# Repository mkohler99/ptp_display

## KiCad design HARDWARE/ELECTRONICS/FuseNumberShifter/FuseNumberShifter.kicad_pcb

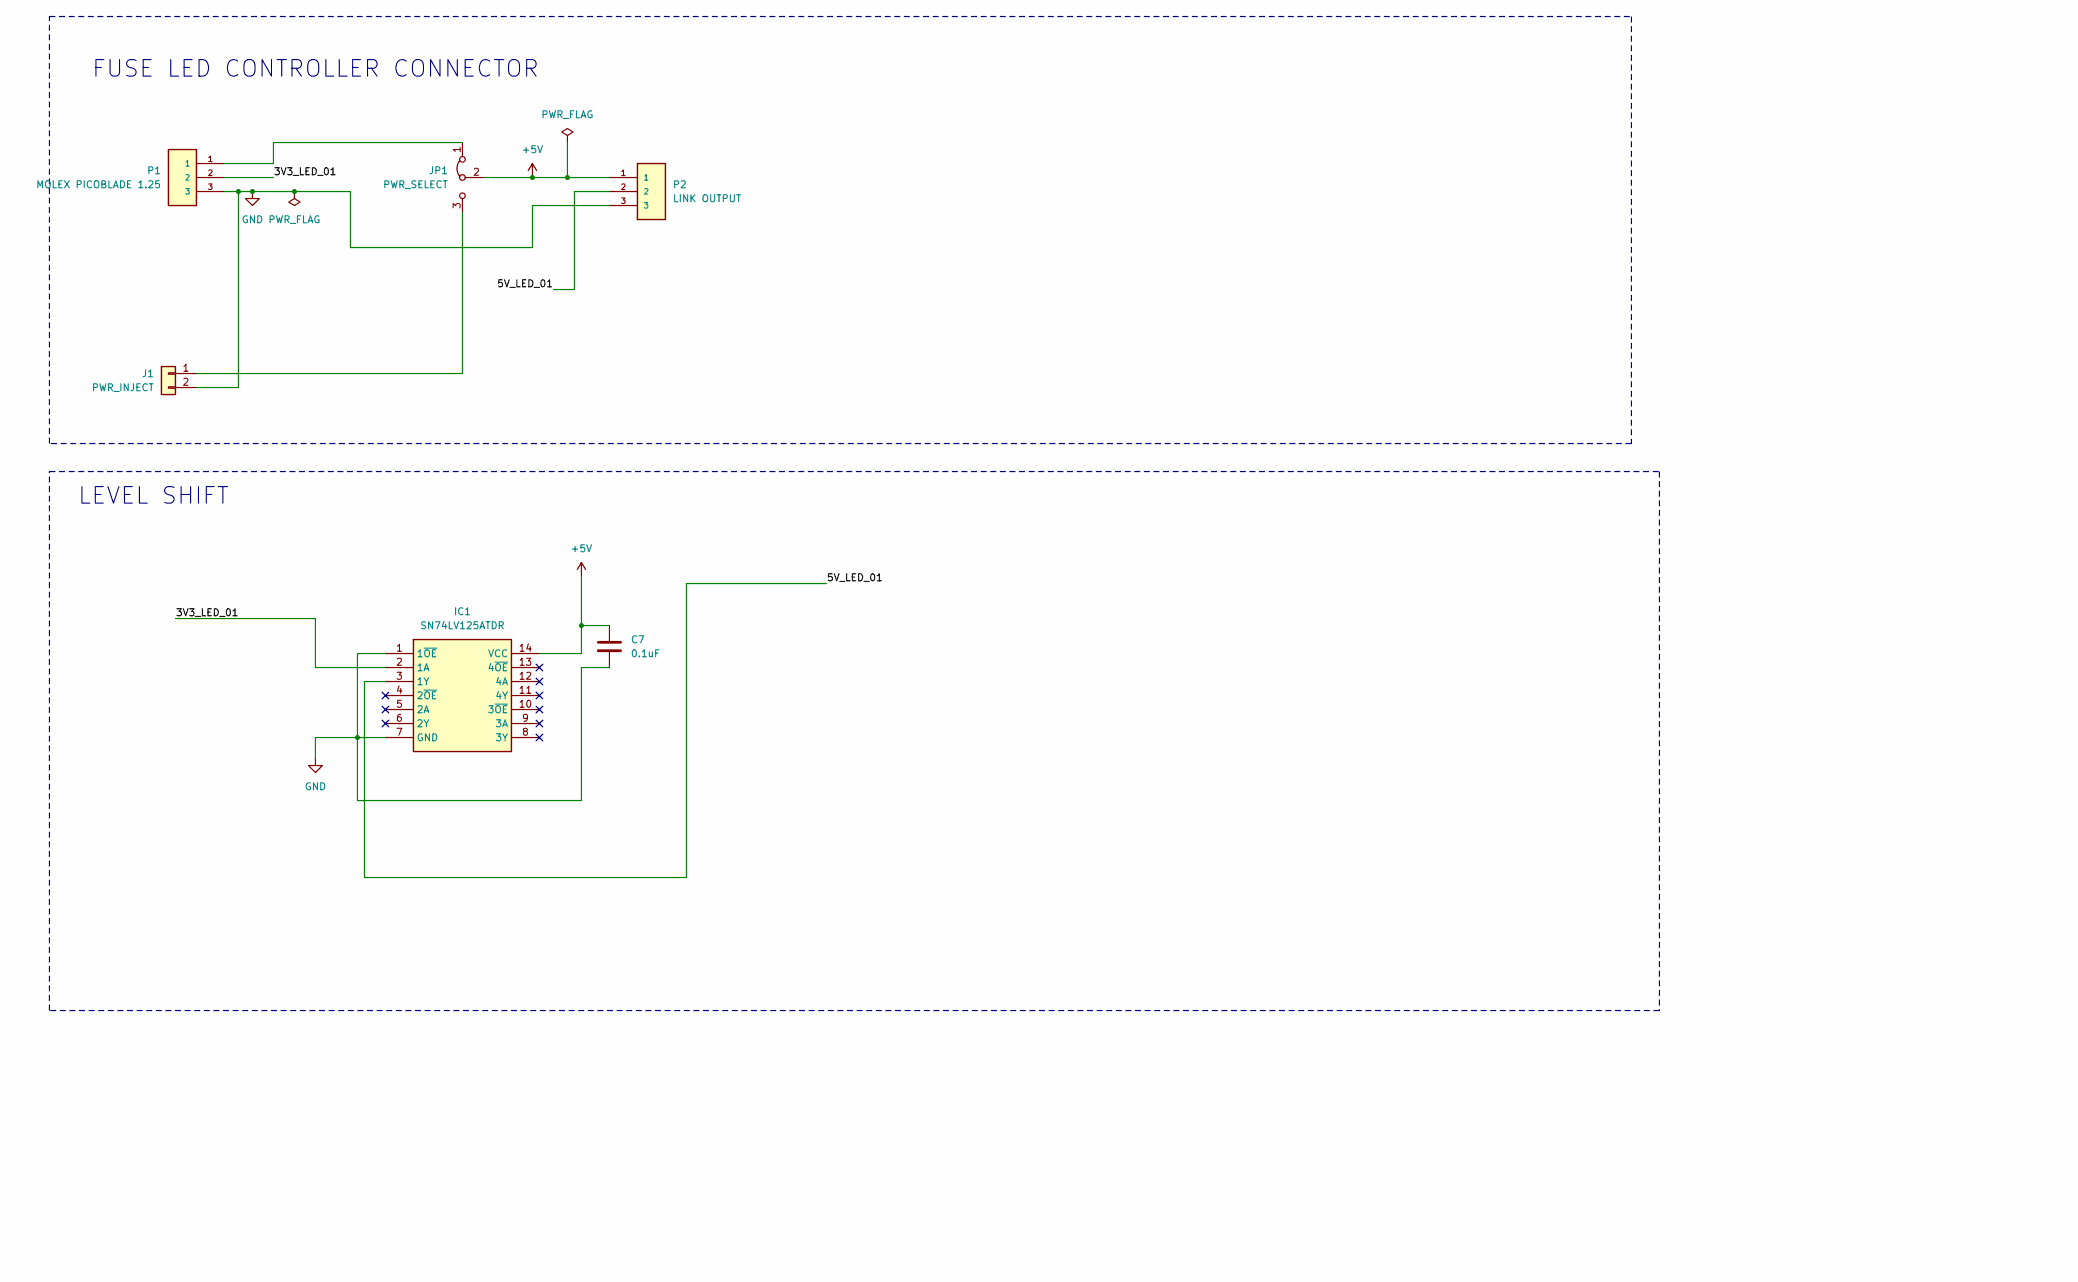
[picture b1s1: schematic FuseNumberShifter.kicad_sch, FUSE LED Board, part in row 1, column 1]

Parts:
C7: 0.1uF; C_0805_2012Metric_Pad1.18x1.45mm_HandSolder
H1, H2, H3, H4: MountingHole; MountingHole_3.2mm_M3
IC1: SN74LV125ATDR; SOIC127P600X175-14N; Mouser Part Number 595-SN74LV125ATDR
J1: PWR_INJECT; PinHeader_1x02_P2.54mm_Horizontal
JP1: PWR_SELECT; SolderJumper-3_P2.0mm_Open_TrianglePad1.0x1.5mm_NumberLabels
P1: MOLEX PICOBLADE 1.25; Molex_PicoBlade_53261-0371_1x03-1MP_P1.25mm_Horizontal
P2: LINK OUTPUT; PinSocket_1x03_P2.54mm_Horizontal

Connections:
+5V: C7.1, IC1.14 (VCC), JP1.2 (C), P2.1
/3V3_LED_01: IC1.2 (1A), P1.2
/5V_LED_01: IC1.3 (1Y), P2.2
GND: C7.2, IC1.1 (1~OE), IC1.7 (GND), J1.2, P1.3, P2.3
unnamed: J1.1, JP1.3 (B)
unnamed: JP1.1 (A), P1.1

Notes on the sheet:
FUSE LED CONTROLLER CONNECTOR
LEVEL SHIFT

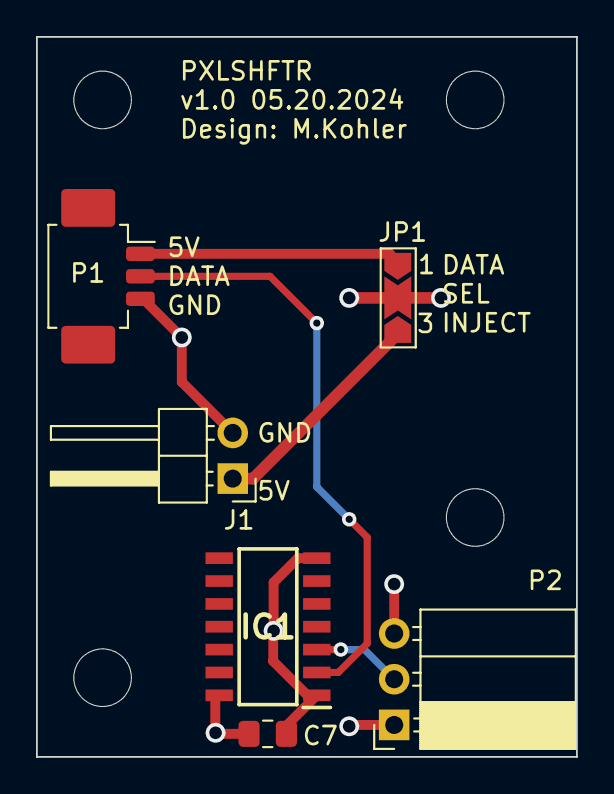
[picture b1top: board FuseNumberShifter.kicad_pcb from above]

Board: 4 copper layers, 30.0 x 40.0 mm, 10 parts (0 on the bottom side), 6 nets.

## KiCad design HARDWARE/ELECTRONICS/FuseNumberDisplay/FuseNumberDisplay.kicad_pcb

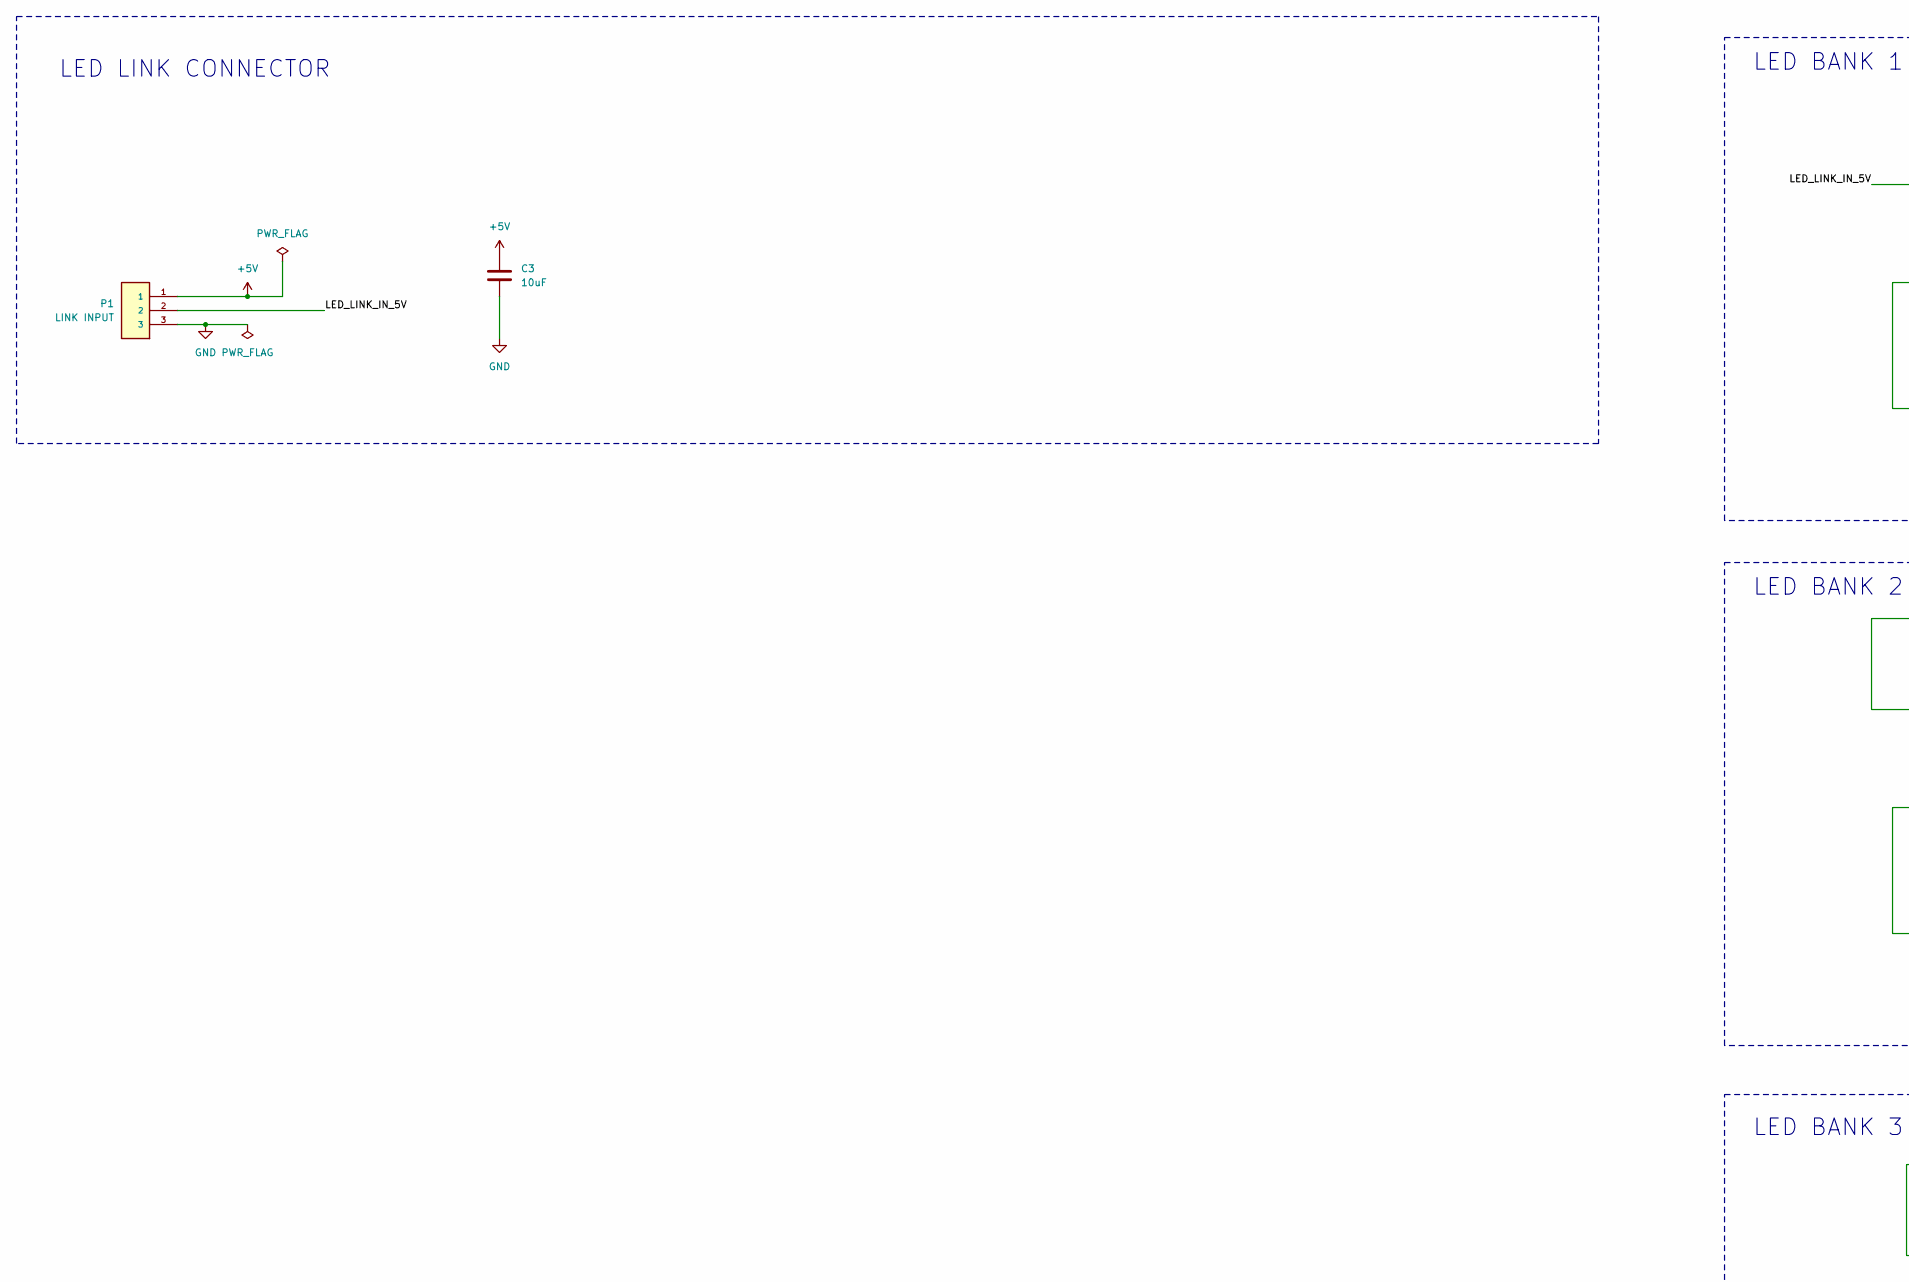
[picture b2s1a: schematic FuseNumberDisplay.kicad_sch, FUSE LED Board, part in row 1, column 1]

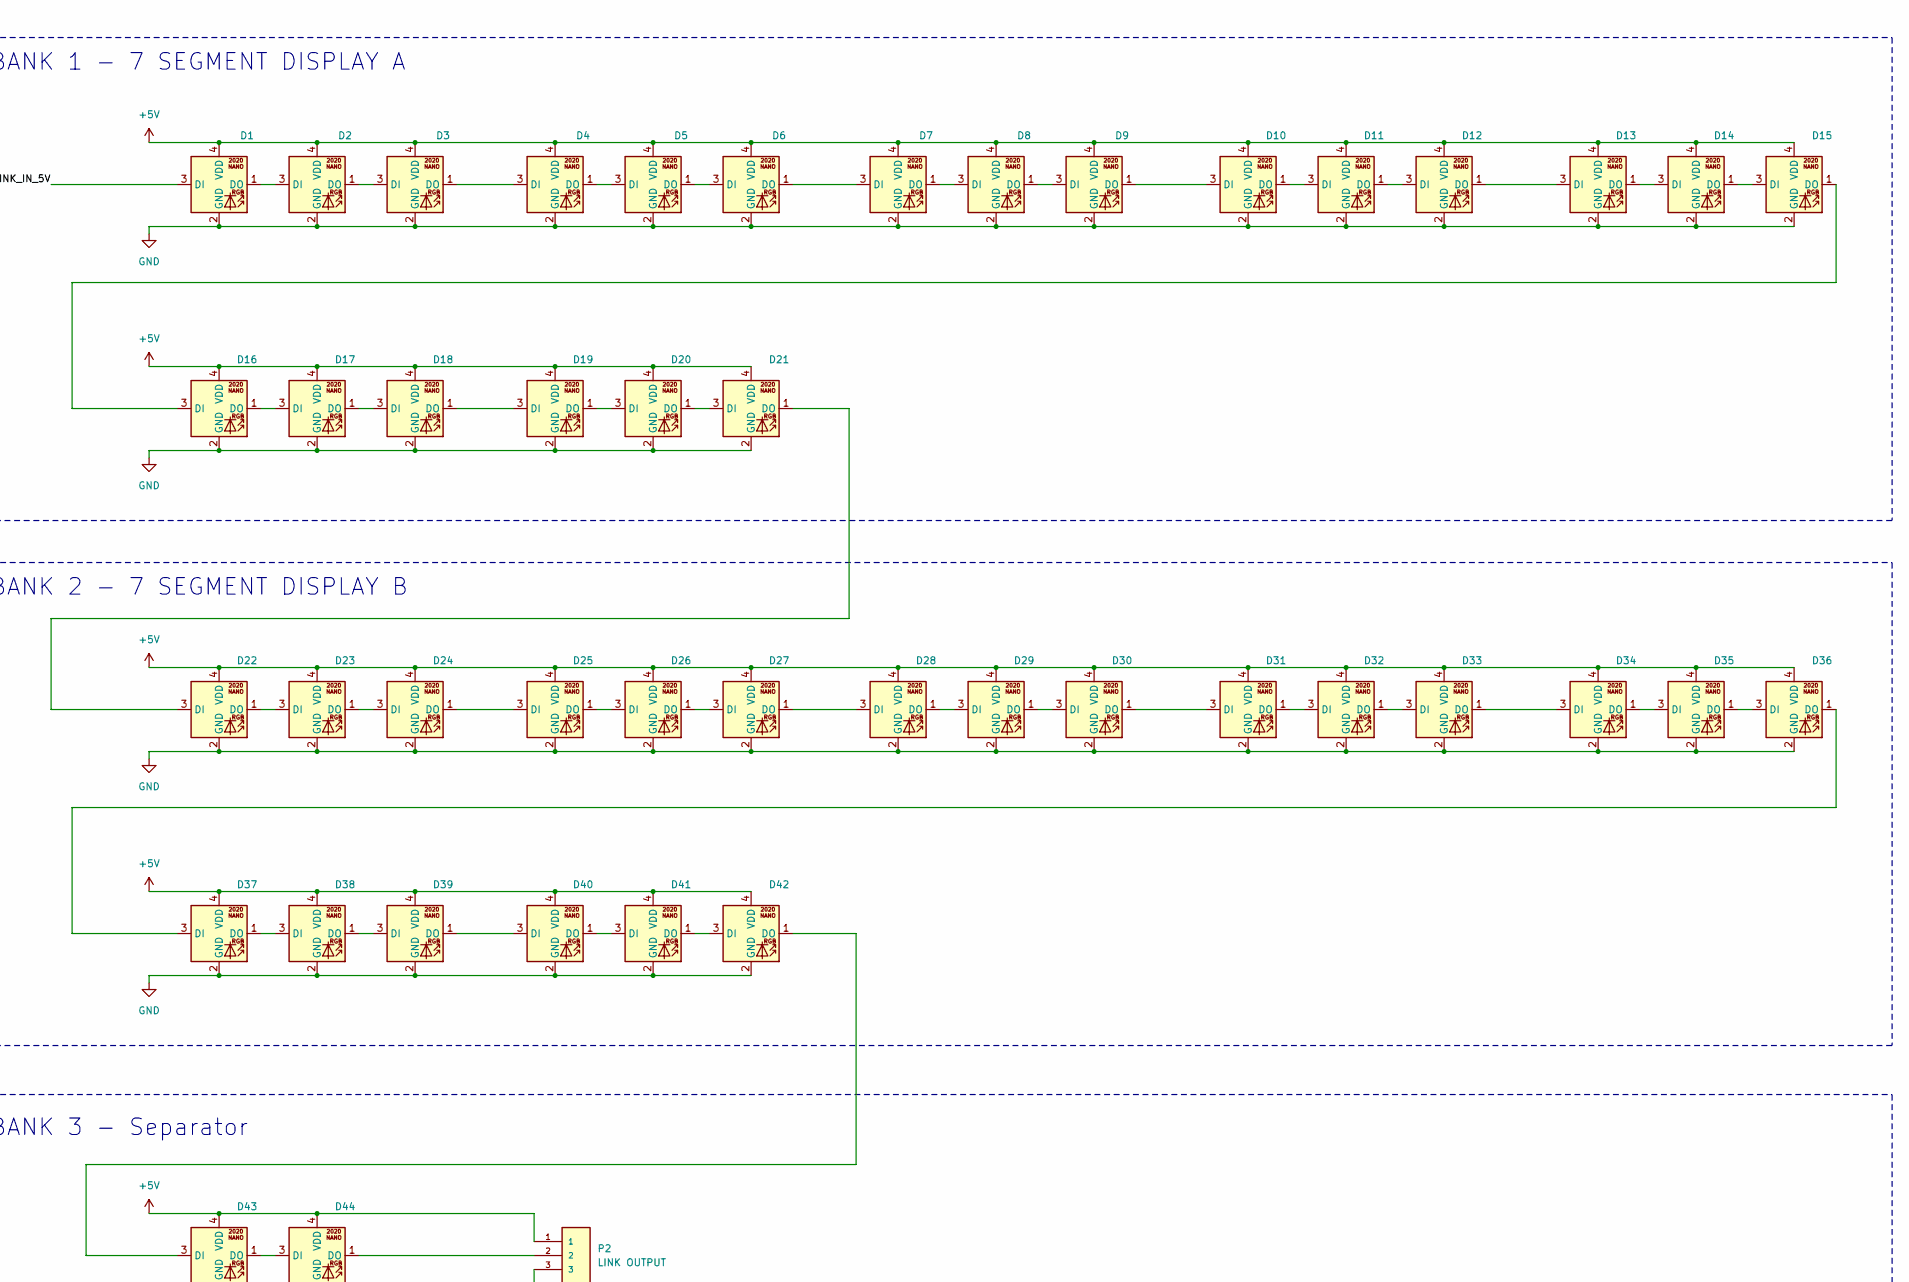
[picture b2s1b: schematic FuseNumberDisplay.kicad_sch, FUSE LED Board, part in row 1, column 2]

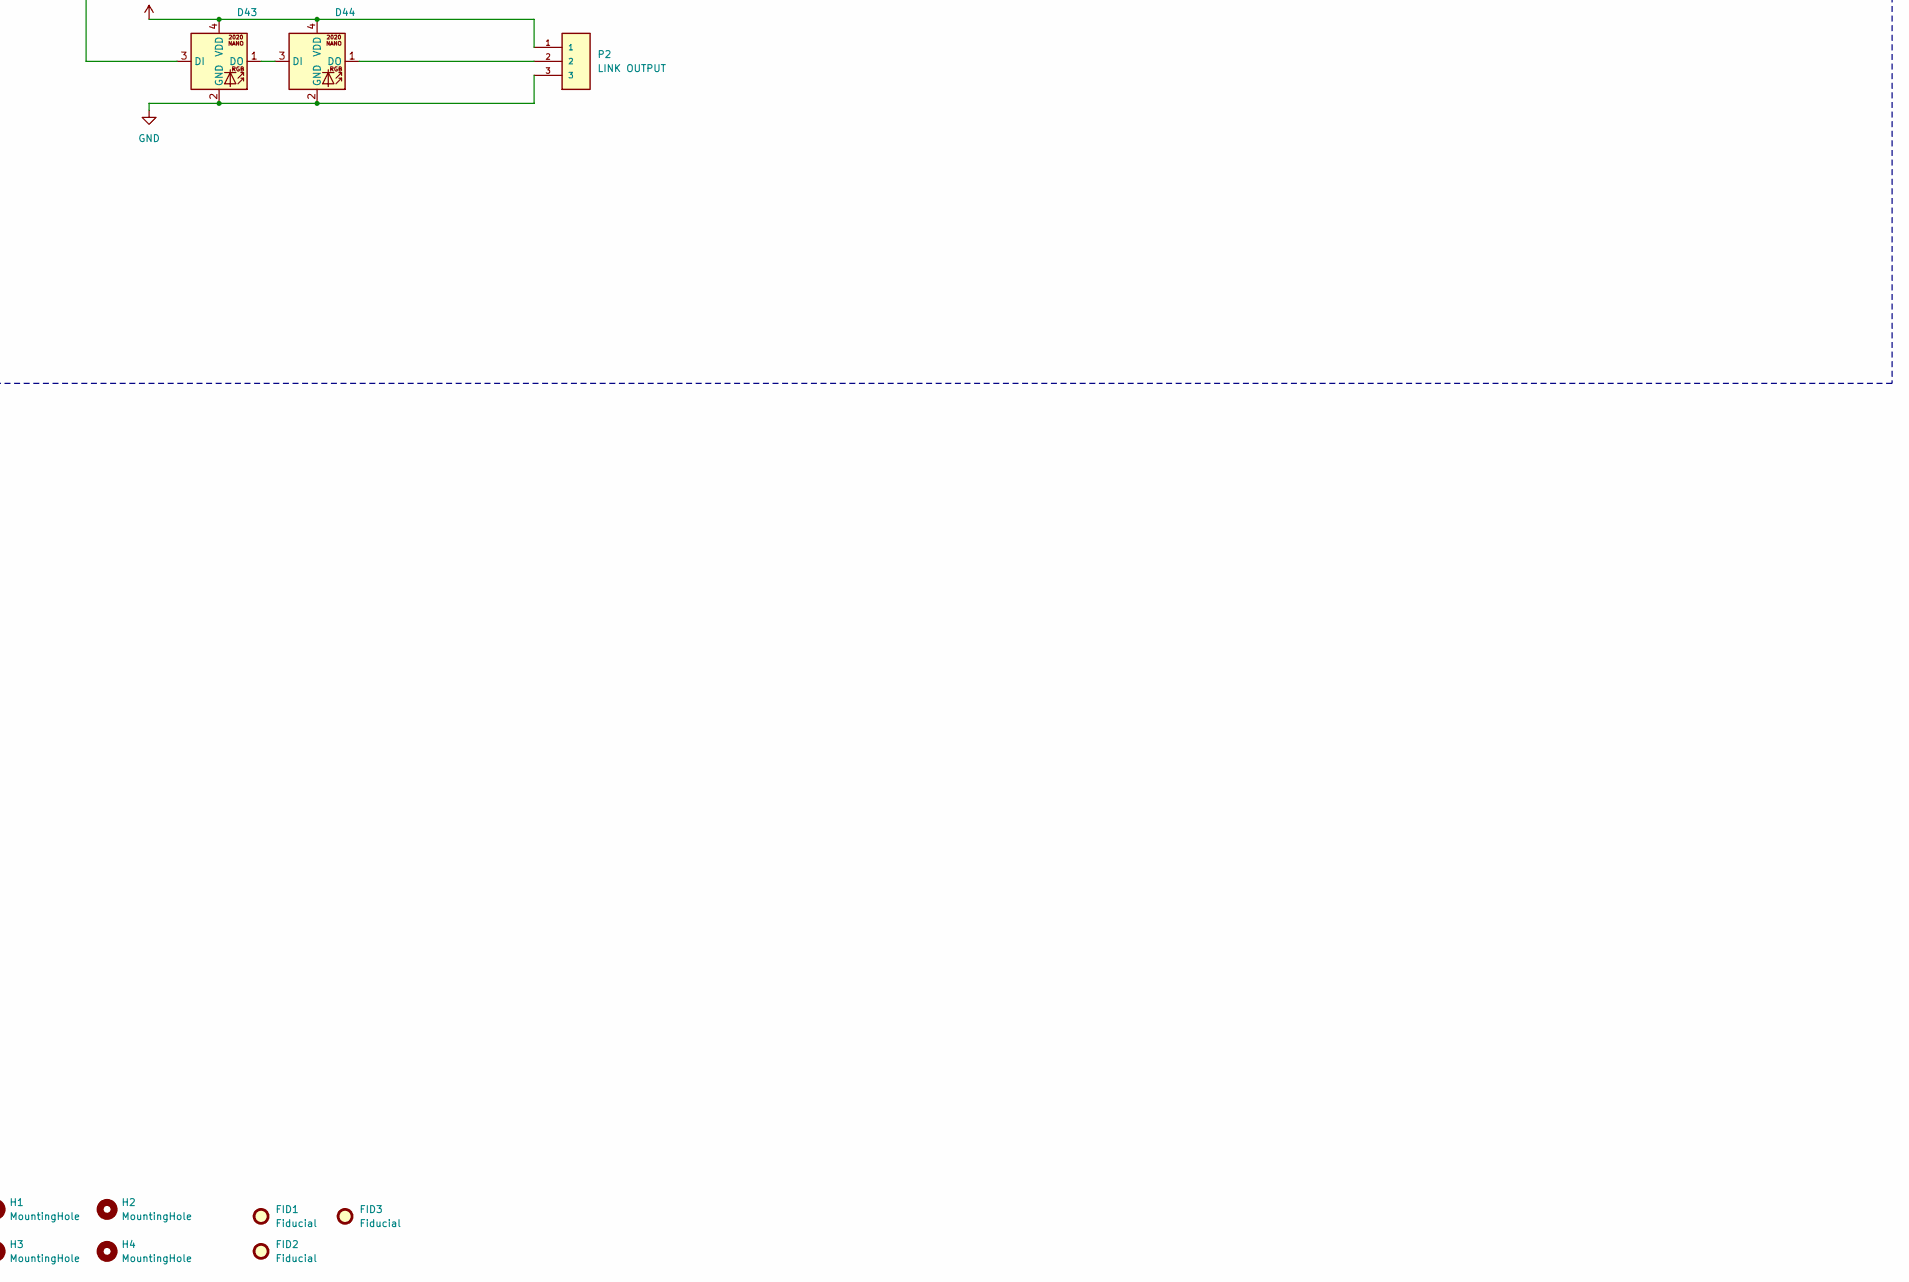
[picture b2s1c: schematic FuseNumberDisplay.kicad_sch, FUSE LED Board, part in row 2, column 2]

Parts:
C3: 10uF; C_0805_2012Metric_Pad1.18x1.45mm_HandSolder
D1, D2, D3, D4, D5, D6, D7, D8, D9, D10, D11, D12, D13, D14, D15, D16, D17, D18, D19, D20, D21, D22, D23, D24, D25, D26, D27, D28, D29, D30, D31, D32, D33, D34, D35, D36, D37, D38, D39, D40, D41, D42, D43, D44: LED_WS2812B-2020_PLCC4_2.0x2.0mm
FID1, FID2, FID3: Fiducial; Fiducial_1mm_Mask2mm
H1, H2, H3, H4: MountingHole; MountingHole_3.2mm_M3
P1: LINK INPUT; PinHeader_1x03_P2.54mm_Horizontal
P2: LINK OUTPUT; PinSocket_1x03_P2.54mm_Horizontal

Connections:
+5V: C3.1, D1.4 (VDD), D2.4 (VDD), D3.4 (VDD), D4.4 (VDD), D5.4 (VDD), D6.4 (VDD), D7.4 (VDD), D8.4 (VDD), D9.4 (VDD), D10.4 (VDD), D11.4 (VDD), D12.4 (VDD), D13.4 (VDD), D14.4 (VDD), D15.4 (VDD), D16.4 (VDD), D17.4 (VDD), D18.4 (VDD), D19.4 (VDD), D20.4 (VDD), D21.4 (VDD), D22.4 (VDD), D23.4 (VDD), D24.4 (VDD), D25.4 (VDD), D26.4 (VDD), D27.4 (VDD), D28.4 (VDD), D29.4 (VDD), D30.4 (VDD), D31.4 (VDD), D32.4 (VDD), D33.4 (VDD), D34.4 (VDD), D35.4 (VDD), D36.4 (VDD), D37.4 (VDD), D38.4 (VDD), D39.4 (VDD), D40.4 (VDD), D41.4 (VDD), D42.4 (VDD), D43.4 (VDD), D44.4 (VDD), P1.1, P2.1
/LED_LINK_IN_5V: D1.3 (DI), P1.2
GND: C3.2, D1.2 (GND), D2.2 (GND), D3.2 (GND), D4.2 (GND), D5.2 (GND), D6.2 (GND), D7.2 (GND), D8.2 (GND), D9.2 (GND), D10.2 (GND), D11.2 (GND), D12.2 (GND), D13.2 (GND), D14.2 (GND), D15.2 (GND), D16.2 (GND), D17.2 (GND), D18.2 (GND), D19.2 (GND), D20.2 (GND), D21.2 (GND), D22.2 (GND), D23.2 (GND), D24.2 (GND), D25.2 (GND), D26.2 (GND), D27.2 (GND), D28.2 (GND), D29.2 (GND), D30.2 (GND), D31.2 (GND), D32.2 (GND), D33.2 (GND), D34.2 (GND), D35.2 (GND), D36.2 (GND), D37.2 (GND), D38.2 (GND), D39.2 (GND), D40.2 (GND), D41.2 (GND), D42.2 (GND), D43.2 (GND), D44.2 (GND), P1.3, P2.3
unnamed: D1.1 (DO), D2.3 (DI)
unnamed: D2.1 (DO), D3.3 (DI)
unnamed: D3.1 (DO), D4.3 (DI)
unnamed: D4.1 (DO), D5.3 (DI)
unnamed: D5.1 (DO), D6.3 (DI)
unnamed: D6.1 (DO), D7.3 (DI)
unnamed: D7.1 (DO), D8.3 (DI)
unnamed: D8.1 (DO), D9.3 (DI)
unnamed: D9.1 (DO), D10.3 (DI)
unnamed: D10.1 (DO), D11.3 (DI)
unnamed: D11.1 (DO), D12.3 (DI)
unnamed: D12.1 (DO), D13.3 (DI)
unnamed: D13.1 (DO), D14.3 (DI)
unnamed: D14.1 (DO), D15.3 (DI)
unnamed: D15.1 (DO), D16.3 (DI)
unnamed: D16.1 (DO), D17.3 (DI)
unnamed: D17.1 (DO), D18.3 (DI)
unnamed: D18.1 (DO), D19.3 (DI)
unnamed: D19.1 (DO), D20.3 (DI)
unnamed: D20.1 (DO), D21.3 (DI)
unnamed: D21.1 (DO), D22.3 (DI)
unnamed: D22.1 (DO), D23.3 (DI)
unnamed: D23.1 (DO), D24.3 (DI)
unnamed: D24.1 (DO), D25.3 (DI)
unnamed: D25.1 (DO), D26.3 (DI)
unnamed: D26.1 (DO), D27.3 (DI)
unnamed: D27.1 (DO), D28.3 (DI)
unnamed: D28.1 (DO), D29.3 (DI)
unnamed: D29.1 (DO), D30.3 (DI)
unnamed: D30.1 (DO), D31.3 (DI)
unnamed: D31.1 (DO), D32.3 (DI)
unnamed: D32.1 (DO), D33.3 (DI)
unnamed: D33.1 (DO), D34.3 (DI)
unnamed: D34.1 (DO), D35.3 (DI)
unnamed: D35.1 (DO), D36.3 (DI)
unnamed: D36.1 (DO), D37.3 (DI)
unnamed: D37.1 (DO), D38.3 (DI)
unnamed: D38.1 (DO), D39.3 (DI)
unnamed: D39.1 (DO), D40.3 (DI)
unnamed: D40.1 (DO), D41.3 (DI)
unnamed: D41.1 (DO), D42.3 (DI)
unnamed: D42.1 (DO), D43.3 (DI)
unnamed: D43.1 (DO), D44.3 (DI)
unnamed: D44.1 (DO), P2.2

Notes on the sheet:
LED BANK 1 - 7 SEGMENT DISPLAY A
LED LINK CONNECTOR
LED BANK 3 - Separator
LED BANK 2 - 7 SEGMENT DISPLAY B

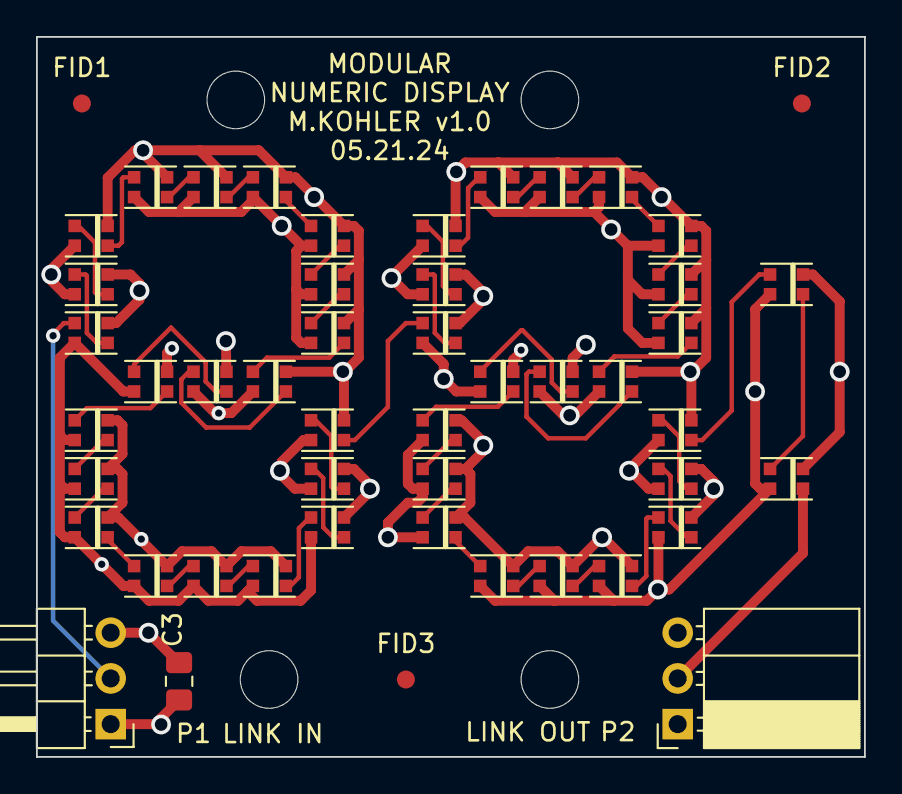
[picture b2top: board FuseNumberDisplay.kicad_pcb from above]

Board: 4 copper layers, 46.0 x 40.0 mm, 54 parts (0 on the bottom side), 47 nets.

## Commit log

2025-02-24 initial
